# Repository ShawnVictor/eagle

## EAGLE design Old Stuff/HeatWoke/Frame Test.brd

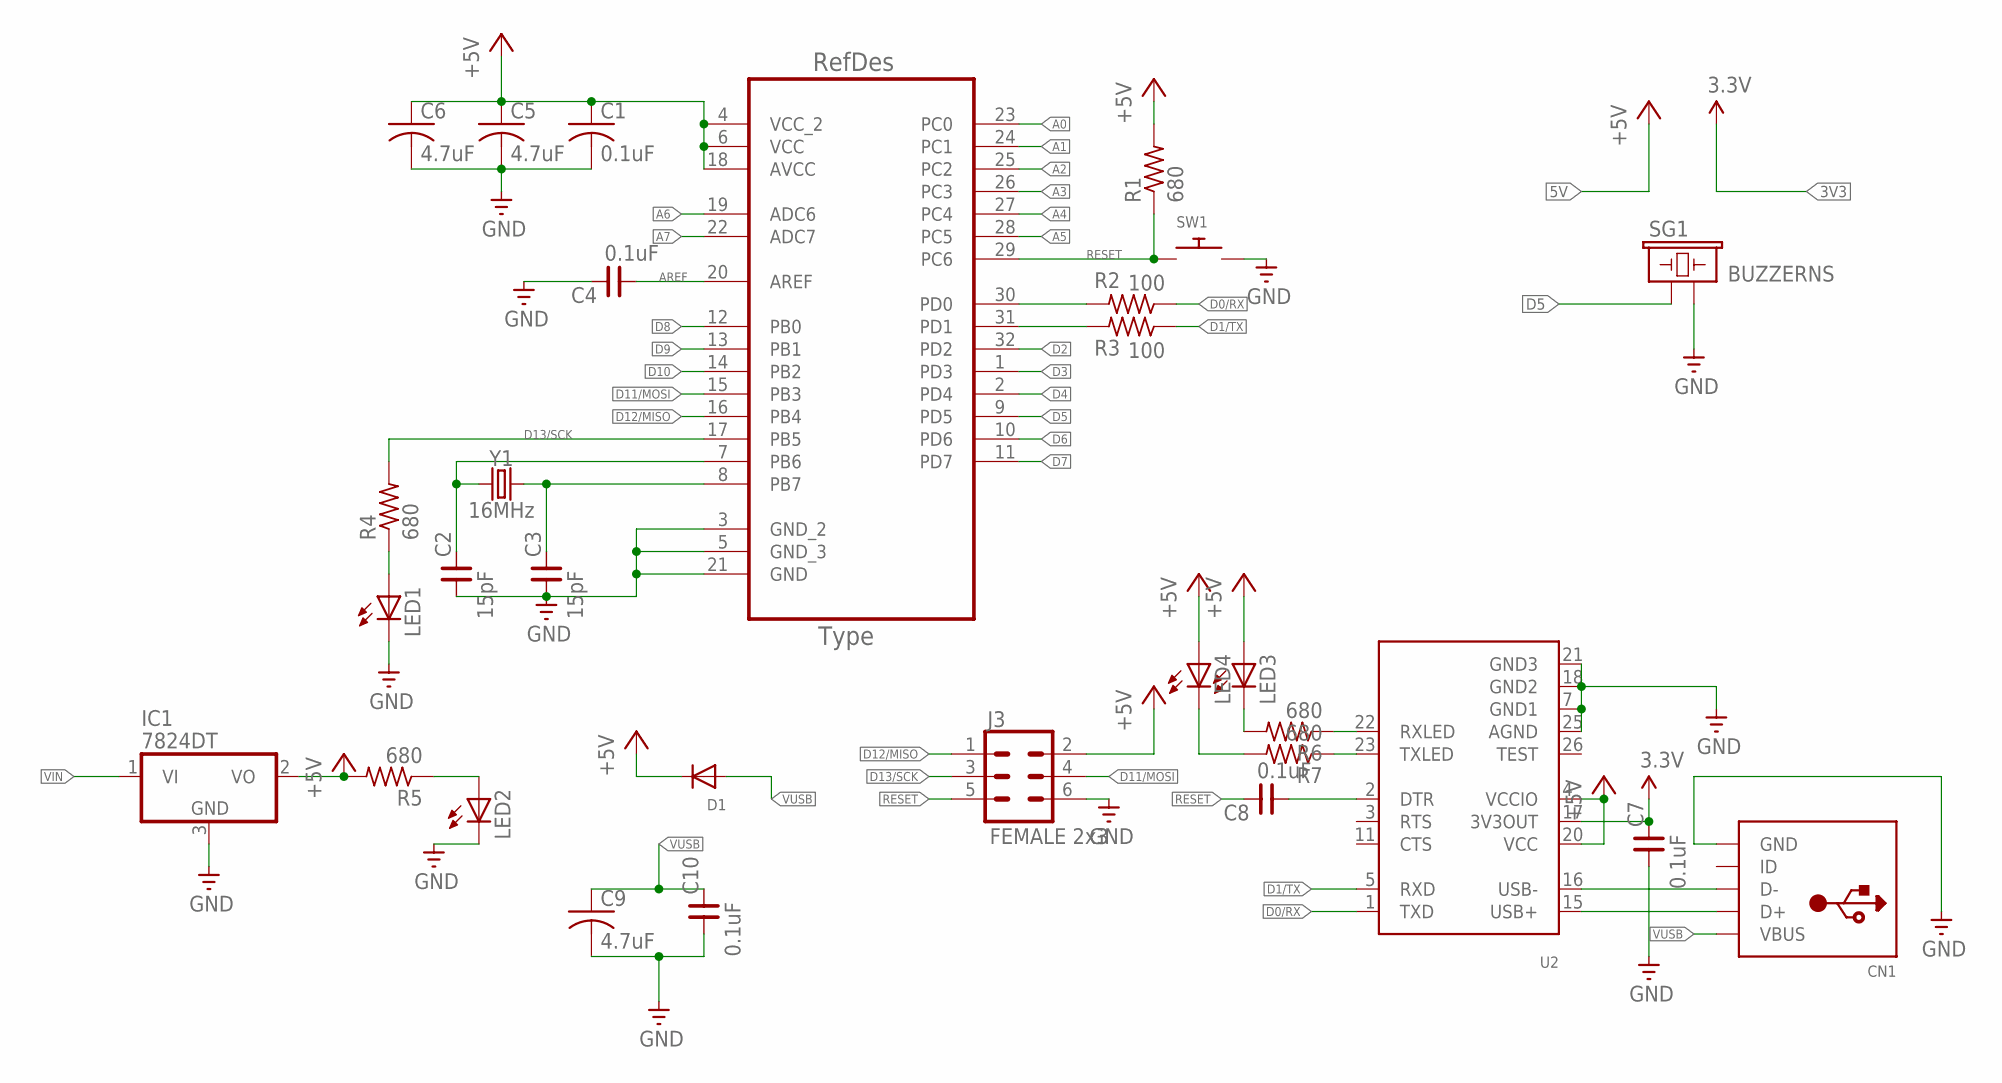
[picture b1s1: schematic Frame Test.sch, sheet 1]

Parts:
C1: 0.1uF; C0805
C2, C3: 15pF; 0805
C4, C7, C8, C10: 0.1uF; 0805
C5, C6, C9: 4.7uF; C0805
CN1: USBMINIB; USB-MINIB
D1: DIODESOD-123; SOD-123
IC1: 7824DT; TO252
J3: FEMALE 2x3; 2X3
LED1, LED2, LED3, LED4: LEDCHIPLED_0805; CHIPLED_0805
R1, R4, R5, R6, R7: 680; R0805
R2, R3: 100; R0805
SG1: BUZZERNS; BUZZER-12MM-NS
SW1: SWITCH_PUSHBUTTONEVQ-PE; TACT_PANA-EVQ
U1: ATMEGA328P-AU; QFP80P900X900X120-32N
U2: FT232RLSSOP28; SSOP28DB
Y1: 16MHz; HC49US

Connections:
3.3V: C7.2, U2.17 (3V3OUT)
+5V: C1.1, C5.1, C6.1, D1.C, IC1.2 (VO), J3.2, LED3.A, LED4.A, R1.2, R5.2, U1.4 (VCC_2), U1.6 (VCC), U1.18 (AVCC), U2.4 (VCCIO), U2.20 (VCC)
A0: U1.23 (PC0)
A1: U1.24 (PC1)
A2: U1.25 (PC2)
A3: U1.26 (PC3)
A4: U1.27 (PC4); also elsewhere on the board
A5: U1.28 (PC5); also elsewhere on the board
A6: U1.19 (ADC6)
A7: U1.22 (ADC7)
AREF: C4.1, U1.20 (AREF)
D0/RX: R2.1, U2.1 (TXD)
D1/TX: R3.1, U2.5 (RXD)
D2: U1.32 (PD2); also elsewhere on the board
D3: U1.1 (PD3); also elsewhere on the board
D4: U1.2 (PD4); also elsewhere on the board
D5: SG1.+ (1), U1.9 (PD5)
D6: U1.10 (PD6); also elsewhere on the board
D7: U1.11 (PD7)
D8: U1.12 (PB0)
D9: U1.13 (PB1)
D10: U1.14 (PB2)
D11/MOSI: J3.4, U1.15 (PB3)
D12/MISO: J3.1, U1.16 (PB4)
D13/SCK: J3.3, R4.2, U1.17 (PB5)
GND: C1.2, C2.1, C3.1, C4.2, C5.2, C6.2, C7.1, C9.2, C10.1, CN1.GND, IC1.3 (GND), J3.6, LED1.C, LED2.C, SG1.- (2), SW1.P$2, U1.3 (GND_2), U1.5 (GND_3), U1.21 (GND), U2.7 (GND1), U2.18 (GND2), U2.21 (GND3), U2.25 (AGND); also elsewhere on the board
unnamed: C3.2, U1.8 (PB7), Y1.2
unnamed: C2.2, U1.7 (PB6), Y1.1
unnamed: CN1.D+, U2.15 (USB+)
unnamed: CN1.D-, U2.16 (USB-)
unnamed: R2.2, U1.30 (PD0)
unnamed: R3.2, U1.31 (PD1)
unnamed: LED3.C, R6.2
unnamed: LED1.A, R4.1
unnamed: LED2.A, R5.1
unnamed: R6.1, U2.22 (RXLED)
unnamed: R7.1, U2.23 (TXLED)
unnamed: C8.1, U2.2 (DTR)
unnamed: LED4.C, R7.2
RESET: C8.2, J3.5, R1.1, SW1.P$1, U1.29 (PC6)
VIN: IC1.1 (VI); also elsewhere on the board
VUSB: C9.1, C10.2, CN1.VBUS, D1.A

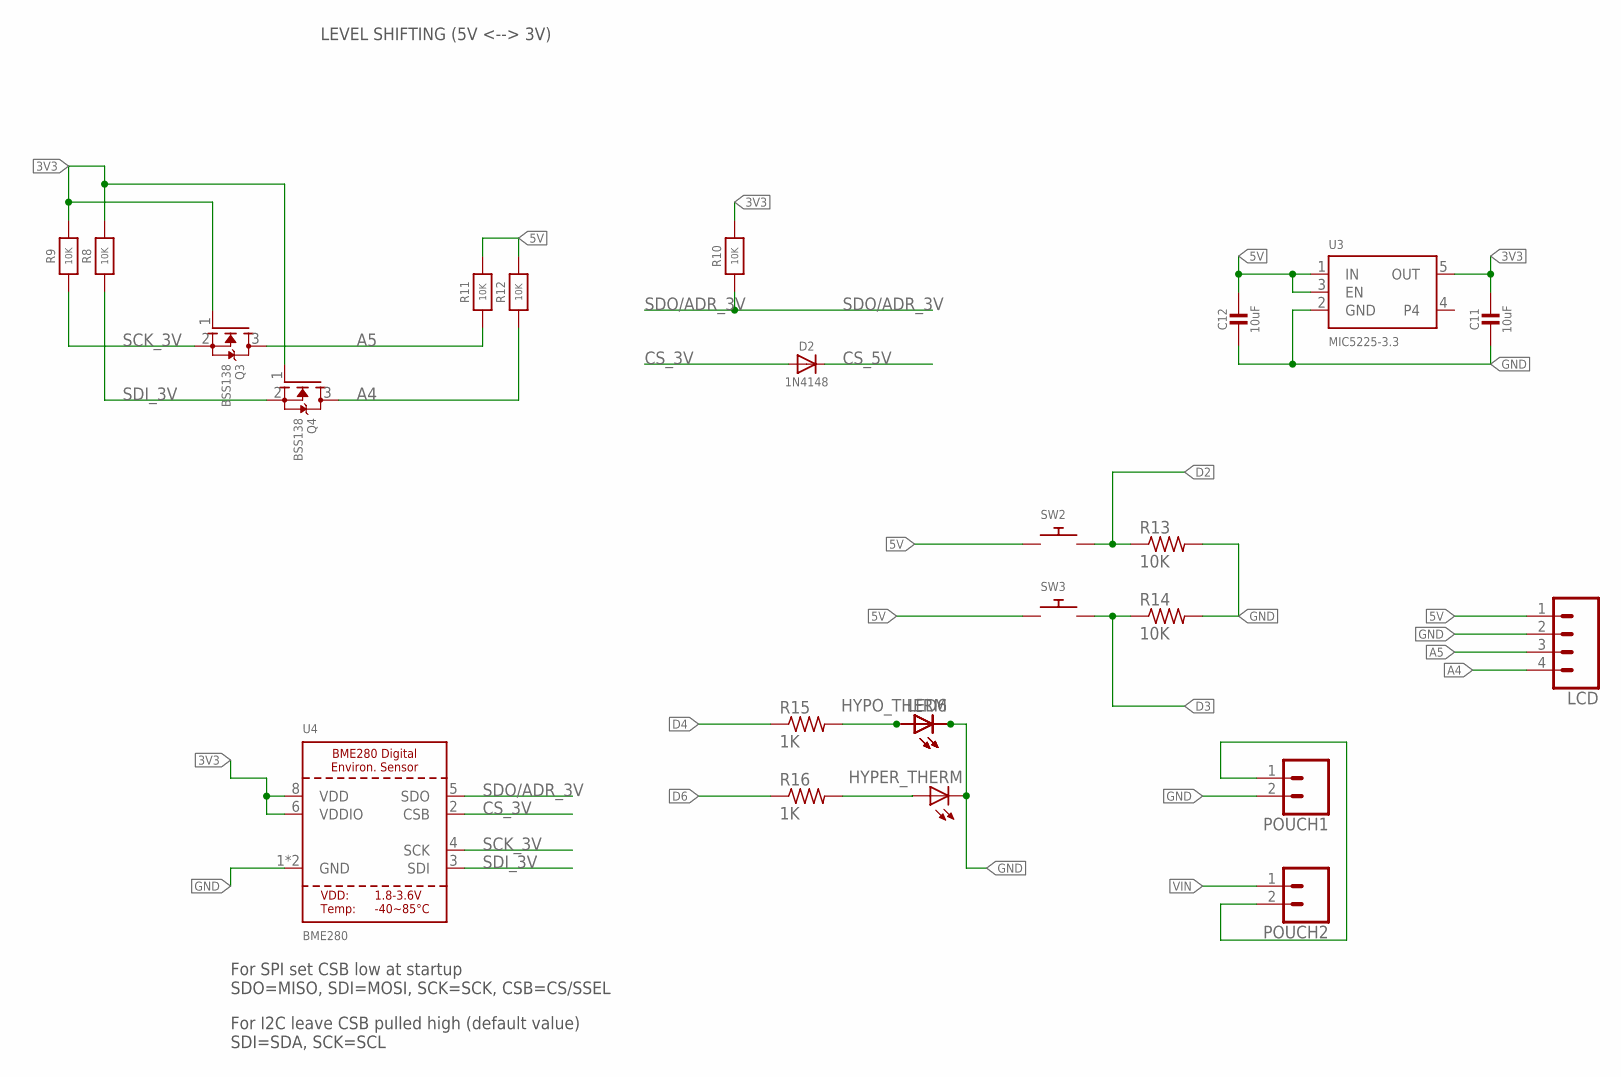
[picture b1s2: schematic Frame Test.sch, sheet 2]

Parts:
C11, C12: 10uF; 0805-NO
D2: 1N4148; SOD-323
HYPER_THERM: LEDCHIPLED_1206; CHIPLED_1206
HYPO_THERM: LEDCHIPLED_1206; CHIPLED_1206
LCD: CONN_04; 1X04
LED6: LEDCHIPLED_1206; CHIPLED_1206
POUCH1, POUCH2: CONN_02; 1X02
Q3, Q4: BSS138; SOT23-WIDE
R8, R9, R11, R12: 10K; 0805-NO
R10: 10K; _0805MP
R13, R14: 10K; R0805
R15, R16: 1K; R0805
SW2, SW3: SWITCH_PUSHBUTTONEVQ-PE; TACT_PANA-EVQ
U3: MIC5225-3.3; SOT23-5
U4: BME280

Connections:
3V3: C11.1, Q3.1 (G), Q4.1 (G), R8.2, R9.2, R10.2, U3.5 (OUT), U4.6 (VDDIO), U4.8 (VDD)
5V: C12.1, LCD.1, R11.2, R12.2, SW2.P$1, SW3.P$1, U3.1 (IN), U3.3 (EN)
A4: LCD.4, Q4.3 (D), R12.1; also elsewhere on the board
A5: LCD.3, Q3.3 (D), R11.1; also elsewhere on the board
CS_3V: D2.A, U4.2 (CSB)
CS_5V: D2.C
D2: R13.1, SW2.P$2; also elsewhere on the board
D3: R14.1, SW3.P$2; also elsewhere on the board
D4: R15.1; also elsewhere on the board
D6: R16.1; also elsewhere on the board
GND: C11.2, C12.2, HYPER_THERM.C, HYPO_THERM.C, LCD.2, LED6.C, POUCH1.2, R13.2, R14.2, U3.2 (GND), U4.1 (GND), U4.7 (GND); also elsewhere on the board
unnamed: POUCH1.1, POUCH2.2
unnamed: HYPO_THERM.A, LED6.A, R15.2
unnamed: HYPER_THERM.A, R16.2
SCK_3V: Q3.2 (S), R9.1, U4.4 (SCK)
SDI_3V: Q4.2 (S), R8.1, U4.3 (SDI)
SDO/ADR_3V: R10.1, U4.5 (SDO)
VIN: POUCH2.1; also elsewhere on the board

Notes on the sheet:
For SPI set CSB low at startup SDO=MISO, SDI=MOSI, SCK=SCK, CSB=CS/SSEL
For I2C leave CSB pulled high (default value) SDI=SDA, SCK=SCL
LEVEL SHIFTING (5V <--> 3V)

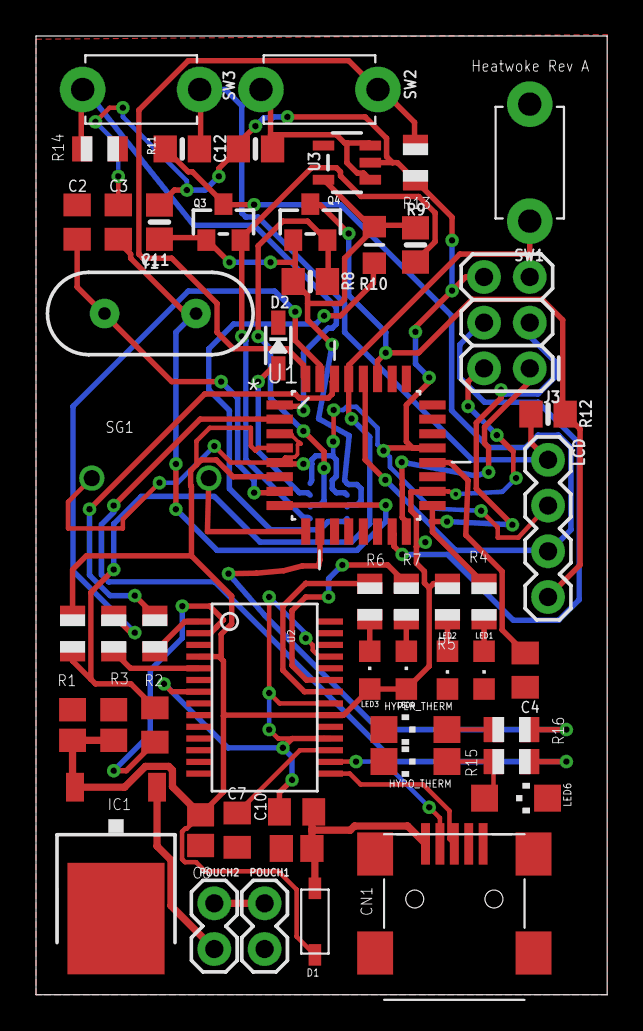
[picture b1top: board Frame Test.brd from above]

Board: 2 copper layers, 31.7 x 53.3 mm, 54 parts (1 on the bottom side), 41 nets.

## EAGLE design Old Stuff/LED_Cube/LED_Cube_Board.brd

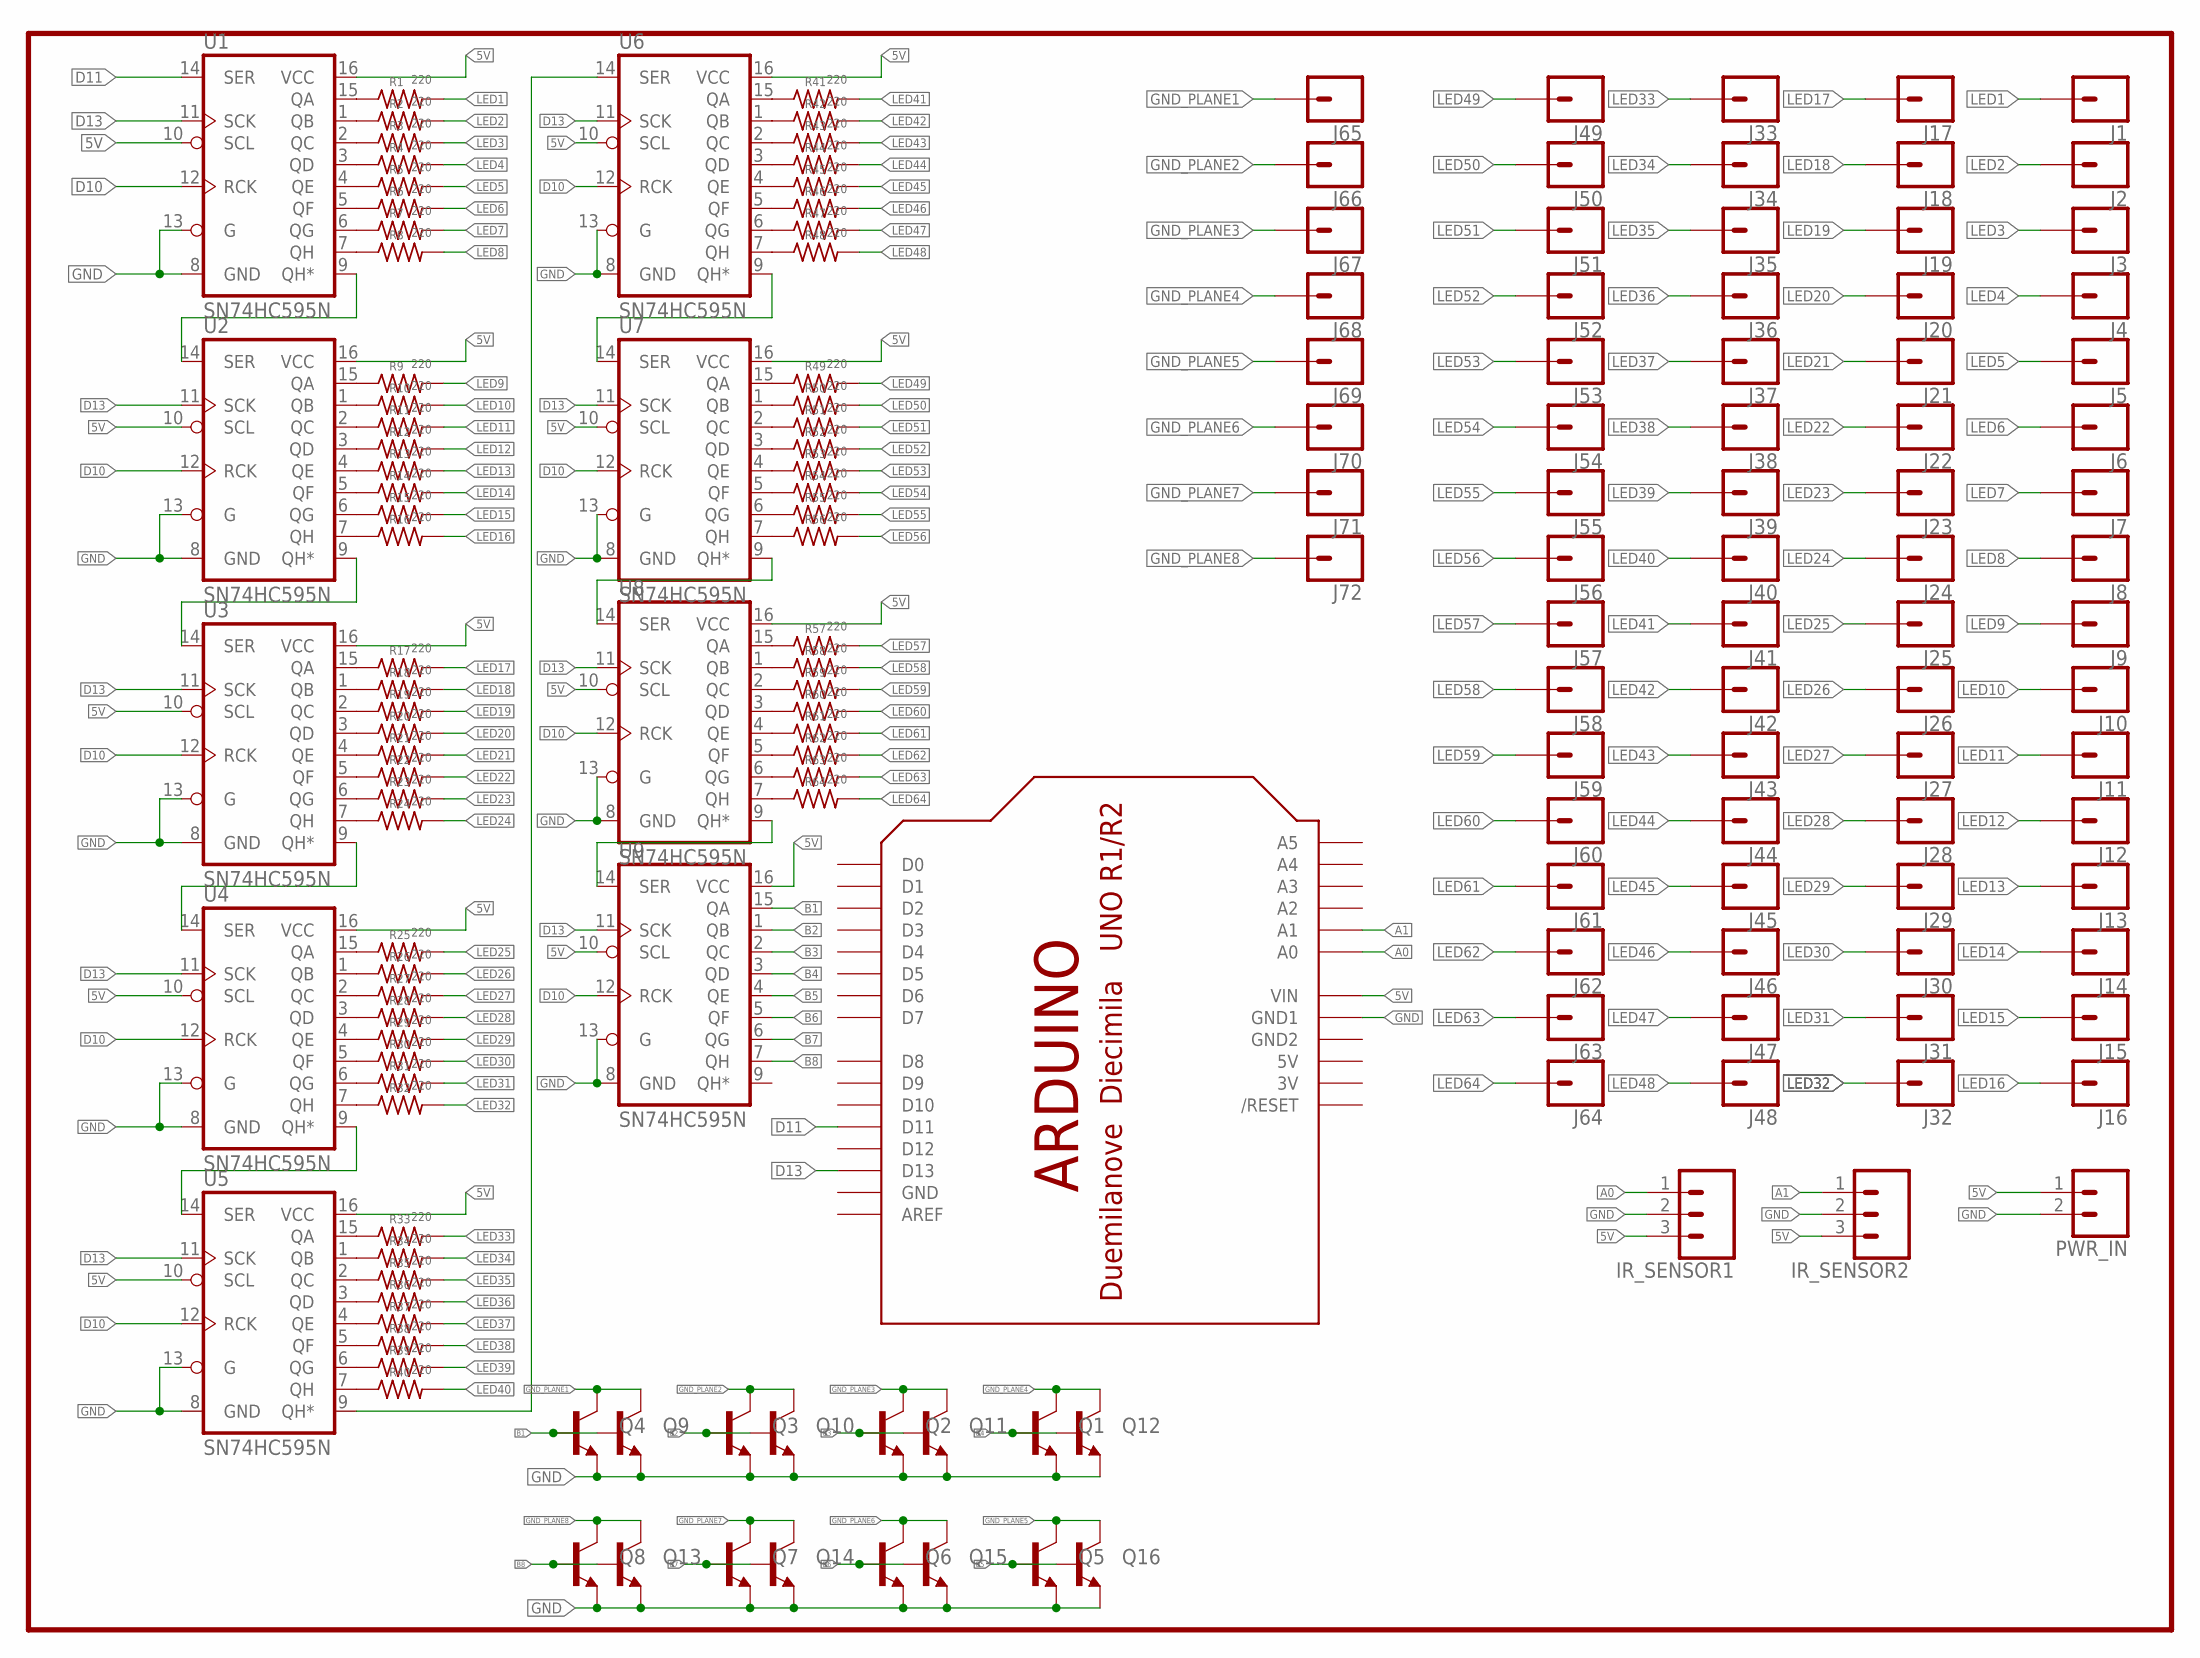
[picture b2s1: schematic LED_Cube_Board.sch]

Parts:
IR_SENSOR1, IR_SENSOR2: CONN_03; 1X03
J1, J2, J3, J4, J5, J6, J7, J8, J9, J10, J11, J12, J13, J14, J15, J16, J17, J18, J19, J20, J21, J22, J23, J24, J25, J26, J27, J28, J29, J30, J31, J32, J33, J34, J35, J36, J37, J38, J39, J40, J41, J42, J43, J44, J45, J46, J47, J48, J49, J50, J51, J52, J53, J54, J55, J56, J57, J58, J59, J60, J61, J62, J63, J64, J65, J66, J67, J68, J69, J70, J71, J72: CONN_01; 1X01
PWR_IN: CONN_02; 1X02
Q1, Q2, Q3, Q4, Q5, Q6, Q7, Q8, Q9, Q10, Q11, Q12, Q13, Q14, Q15, Q16: TRANSISTOR_NPNTO92; TO-92
R1, R2, R3, R4, R5, R6, R7, R8, R9, R10, R11, R12, R13, R14, R15, R16, R17, R18, R19, R20, R21, R22, R23, R24, R25, R26, R27, R28, R29, R30, R31, R32, R33, R34, R35, R36, R37, R38, R39, R40, R41, R42, R43, R44, R45, R46, R47, R48, R49, R50, R51, R52, R53, R54, R55, R56, R57, R58, R59, R60, R61, R62, R63, R64: 220; R0805
U1, U2, U3, U4, U5, U6, U7, U8, U9: SN74HC595N; DIP16
U$1: ARDUINO-BPLACE

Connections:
3V: U$1.3V
5V: IR_SENSOR1.3, IR_SENSOR2.3, PWR_IN.1, U1.10 (SCL), U1.16 (VCC), U2.10 (SCL), U2.16 (VCC), U3.10 (SCL), U3.16 (VCC), U4.10 (SCL), U4.16 (VCC), U5.10 (SCL), U5.16 (VCC), U6.10 (SCL), U6.16 (VCC), U7.10 (SCL), U7.16 (VCC), U8.10 (SCL), U8.16 (VCC), U9.10 (SCL), U9.16 (VCC), U$1.5V, U$1.VIN
A0: IR_SENSOR1.1, U$1.A0
A1: IR_SENSOR2.1, U$1.A1
B1: Q4.2 (B), Q9.2 (B), U9.15 (QA)
B2: Q3.2 (B), Q10.2 (B), U9.1 (QB)
B3: Q2.2 (B), Q11.2 (B), U9.2 (QC)
B4: Q1.2 (B), Q12.2 (B), U9.3 (QD)
B5: Q5.2 (B), Q16.2 (B), U9.4 (QE)
B6: Q6.2 (B), Q15.2 (B), U9.5 (QF)
B7: Q7.2 (B), Q14.2 (B), U9.6 (QG)
B8: Q8.2 (B), Q13.2 (B), U9.7 (QH)
D10: U1.12 (RCK), U2.12 (RCK), U3.12 (RCK), U4.12 (RCK), U5.12 (RCK), U6.12 (RCK), U7.12 (RCK), U8.12 (RCK), U9.12 (RCK)
D11: U1.14 (SER), U$1.D11
D13: U1.11 (SCK), U2.11 (SCK), U3.11 (SCK), U4.11 (SCK), U5.11 (SCK), U6.11 (SCK), U7.11 (SCK), U8.11 (SCK), U9.11 (SCK), U$1.D13
GND: IR_SENSOR1.2, IR_SENSOR2.2, PWR_IN.2, Q1.1 (E), Q2.1 (E), Q3.1 (E), Q4.1 (E), Q5.1 (E), Q6.1 (E), Q7.1 (E), Q8.1 (E), Q9.1 (E), Q10.1 (E), Q11.1 (E), Q12.1 (E), Q13.1 (E), Q14.1 (E), Q15.1 (E), Q16.1 (E), U1.8 (GND), U1.13 (G), U2.8 (GND), U2.13 (G), U3.8 (GND), U3.13 (G), U4.8 (GND), U4.13 (G), U5.8 (GND), U5.13 (G), U6.8 (GND), U6.13 (G), U7.8 (GND), U7.13 (G), U8.8 (GND), U8.13 (G), U9.8 (GND), U9.13 (G), U$1.GND, U$1.GND1
GND2: U$1.GND2
GND_PLANE1: J65.1, Q4.3 (C), Q9.3 (C)
GND_PLANE2: J66.1, Q3.3 (C), Q10.3 (C)
GND_PLANE3: J67.1, Q2.3 (C), Q11.3 (C)
GND_PLANE4: J68.1, Q1.3 (C), Q12.3 (C)
GND_PLANE5: J69.1, Q5.3 (C), Q16.3 (C)
GND_PLANE6: J70.1, Q6.3 (C), Q15.3 (C)
GND_PLANE7: J71.1, Q7.3 (C), Q14.3 (C)
GND_PLANE8: J72.1, Q8.3 (C), Q13.3 (C)
LED1: J1.1, R1.2
LED2: J2.1, R2.2
LED3: J3.1, R3.2
LED4: J4.1, R4.2
LED5: J5.1, R5.2
LED6: J6.1, R6.2
LED7: J7.1, R7.2
LED8: J8.1, R8.2
LED9: J9.1, R9.2
LED10: J10.1, R10.2
LED11: J11.1, R11.2
LED12: J12.1, R12.2
LED13: J13.1, R13.2
LED14: J14.1, R14.2
LED15: J15.1, R15.2
LED16: J16.1, R16.2
LED17: J17.1, R17.2
LED18: J18.1, R18.2
LED19: J19.1, R19.2
LED20: J20.1, R20.2
LED21: J21.1, R21.2
LED22: J22.1, R22.2
LED23: J23.1, R23.2
LED24: J24.1, R24.2
LED25: J25.1, R25.2
LED26: J26.1, R26.2
LED27: J27.1, R27.2
LED28: J28.1, R28.2
LED29: J29.1, R29.2
LED30: J30.1, R30.2
LED31: J31.1, R31.2
LED32: J32.1, R32.2
LED33: J33.1, R33.2
LED34: J34.1, R34.2
LED35: J35.1, R35.2
LED36: J36.1, R36.2
LED37: J37.1, R37.2
LED38: J38.1, R38.2
LED39: J39.1, R39.2
LED40: J40.1, R40.2
LED41: J41.1, R41.2
LED42: J42.1, R42.2
LED43: J43.1, R43.2
LED44: J44.1, R44.2
LED45: J45.1, R45.2
LED46: J46.1, R46.2
LED47: J47.1, R47.2
LED48: J48.1, R48.2
LED49: J49.1, R49.2
LED50: J50.1, R50.2
LED51: J51.1, R51.2
LED52: J52.1, R52.2
LED53: J53.1, R53.2
LED54: J54.1, R54.2
LED55: J55.1, R55.2
LED56: J56.1, R56.2
LED57: J57.1, R57.2
LED58: J58.1, R58.2
LED59: J59.1, R59.2
LED60: J60.1, R60.2
LED61: J61.1, R61.2
LED62: J62.1, R62.2
LED63: J63.1, R63.2
LED64: J64.1, R64.2
unnamed: R1.1, U1.15 (QA)
unnamed: R2.1, U1.1 (QB)
unnamed: R3.1, U1.2 (QC)
unnamed: U1.9 (QH*), U2.14 (SER)
unnamed: U2.9 (QH*), U3.14 (SER)
unnamed: U3.9 (QH*), U4.14 (SER)
unnamed: U4.9 (QH*), U5.14 (SER)
unnamed: U5.9 (QH*), U6.14 (SER)
unnamed: U6.9 (QH*), U7.14 (SER)
unnamed: U7.9 (QH*), U8.14 (SER)
unnamed: R4.1, U1.3 (QD)
unnamed: R5.1, U1.4 (QE)
unnamed: R6.1, U1.5 (QF)
unnamed: R7.1, U1.6 (QG)
unnamed: R8.1, U1.7 (QH)
unnamed: R9.1, U2.15 (QA)
unnamed: R10.1, U2.1 (QB)
unnamed: R11.1, U2.2 (QC)
unnamed: R12.1, U2.3 (QD)
unnamed: R13.1, U2.4 (QE)
unnamed: R14.1, U2.5 (QF)
unnamed: R15.1, U2.6 (QG)
unnamed: R16.1, U2.7 (QH)
unnamed: R17.1, U3.15 (QA)
unnamed: R18.1, U3.1 (QB)
unnamed: R19.1, U3.2 (QC)
unnamed: R20.1, U3.3 (QD)
unnamed: R21.1, U3.4 (QE)
unnamed: R22.1, U3.5 (QF)
unnamed: R23.1, U3.6 (QG)
unnamed: R24.1, U3.7 (QH)
unnamed: R25.1, U4.15 (QA)
unnamed: R26.1, U4.1 (QB)
unnamed: R27.1, U4.2 (QC)
unnamed: R28.1, U4.3 (QD)
unnamed: R29.1, U4.4 (QE)
unnamed: R30.1, U4.5 (QF)
unnamed: R31.1, U4.6 (QG)
unnamed: R32.1, U4.7 (QH)
unnamed: R33.1, U5.15 (QA)
unnamed: R34.1, U5.1 (QB)
unnamed: R35.1, U5.2 (QC)
unnamed: R36.1, U5.3 (QD)
unnamed: R37.1, U5.4 (QE)
unnamed: R38.1, U5.5 (QF)
unnamed: R39.1, U5.6 (QG)
unnamed: R40.1, U5.7 (QH)
unnamed: R41.1, U6.15 (QA)
unnamed: R42.1, U6.1 (QB)
unnamed: R43.1, U6.2 (QC)
unnamed: R44.1, U6.3 (QD)
unnamed: R45.1, U6.4 (QE)
unnamed: R46.1, U6.5 (QF)
unnamed: R47.1, U6.6 (QG)
unnamed: R48.1, U6.7 (QH)
unnamed: R49.1, U7.15 (QA)
unnamed: R50.1, U7.1 (QB)
unnamed: R51.1, U7.2 (QC)
unnamed: R52.1, U7.3 (QD)
unnamed: R53.1, U7.4 (QE)
unnamed: R54.1, U7.5 (QF)
unnamed: R55.1, U7.6 (QG)
unnamed: R56.1, U7.7 (QH)
unnamed: R57.1, U8.15 (QA)
unnamed: R58.1, U8.1 (QB)
unnamed: R59.1, U8.2 (QC)
unnamed: R60.1, U8.3 (QD)
unnamed: R61.1, U8.4 (QE)
unnamed: R62.1, U8.5 (QF)
unnamed: R63.1, U8.6 (QG)
unnamed: R64.1, U8.7 (QH)
unnamed: U8.9 (QH*), U9.14 (SER)

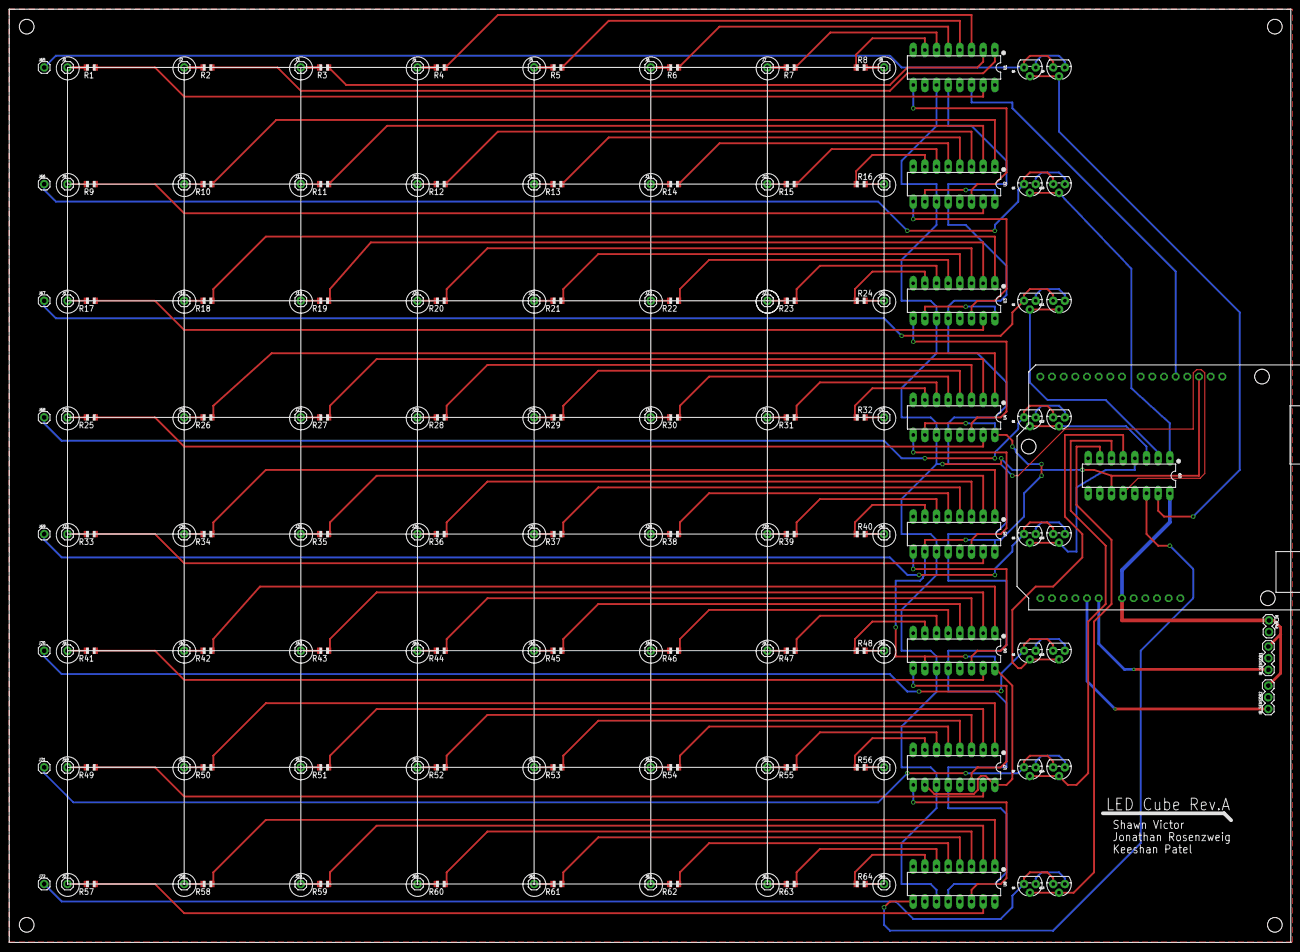
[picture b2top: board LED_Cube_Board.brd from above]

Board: 2 copper layers, 279.1 x 203.2 mm, 165 parts (1 on the bottom side), 159 nets.

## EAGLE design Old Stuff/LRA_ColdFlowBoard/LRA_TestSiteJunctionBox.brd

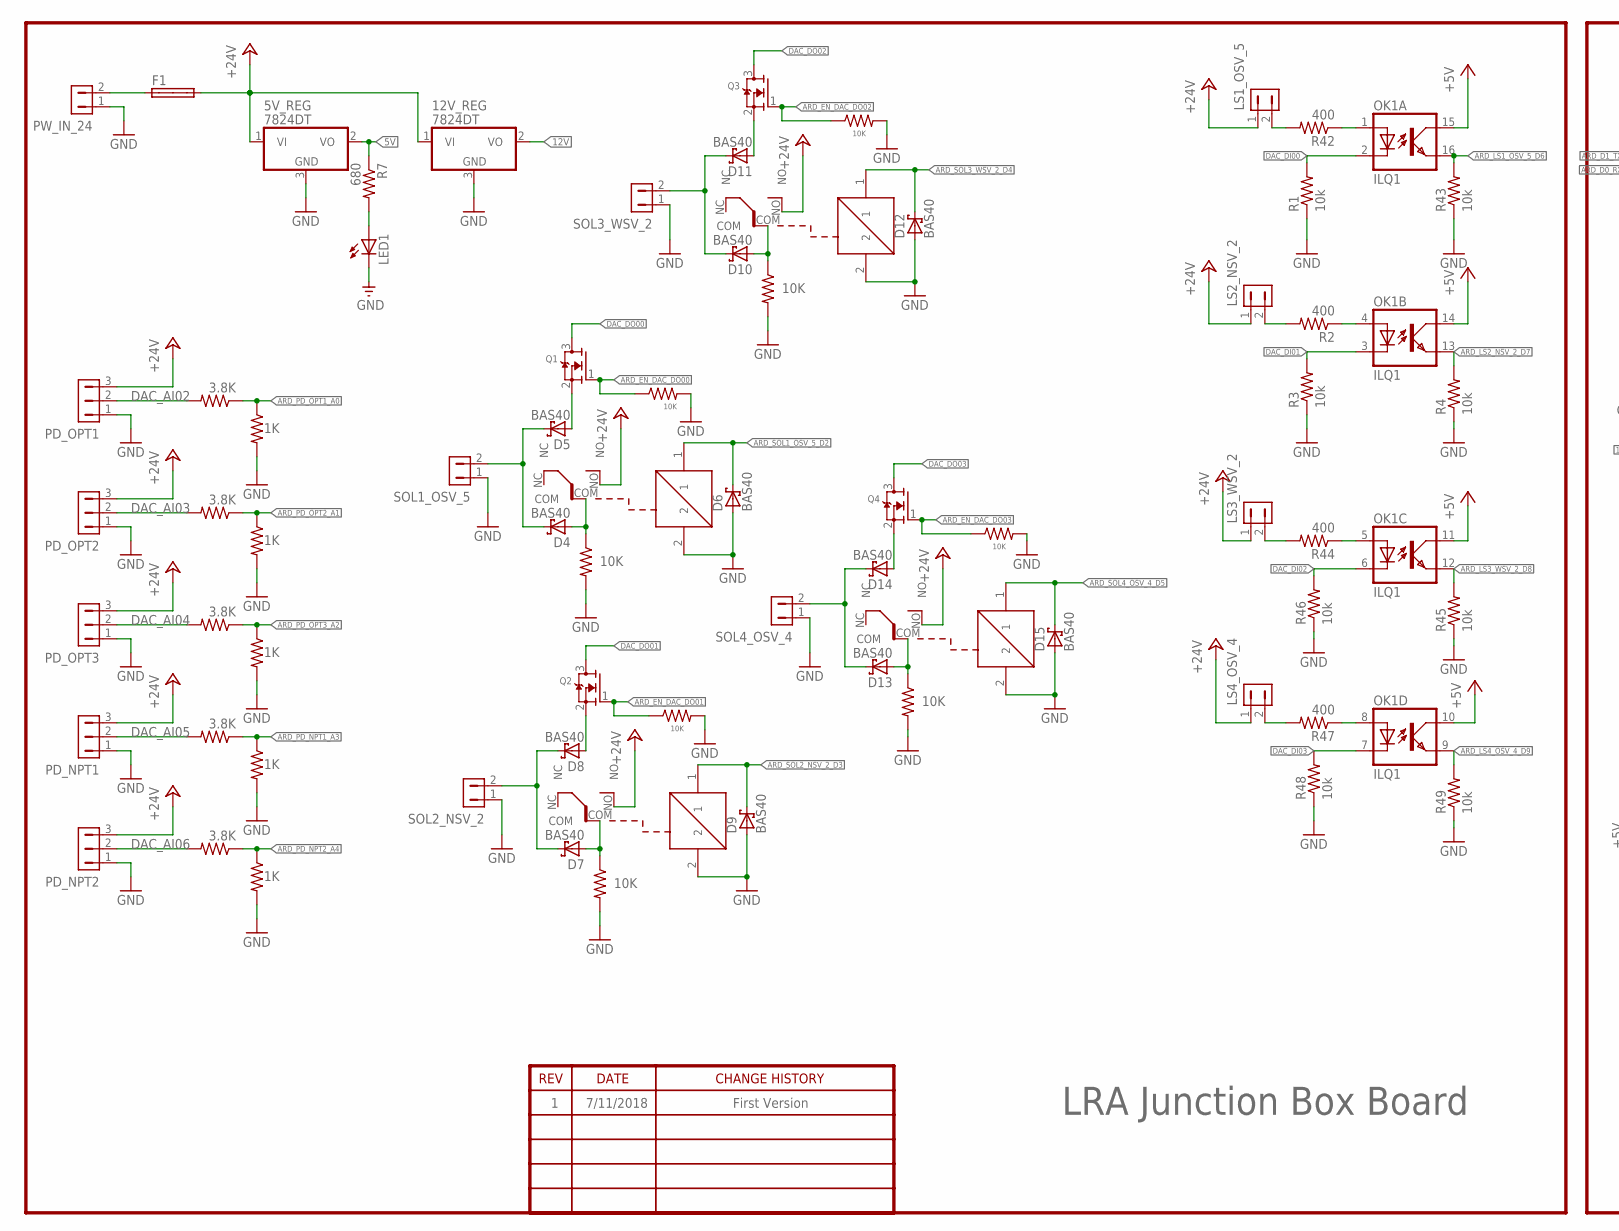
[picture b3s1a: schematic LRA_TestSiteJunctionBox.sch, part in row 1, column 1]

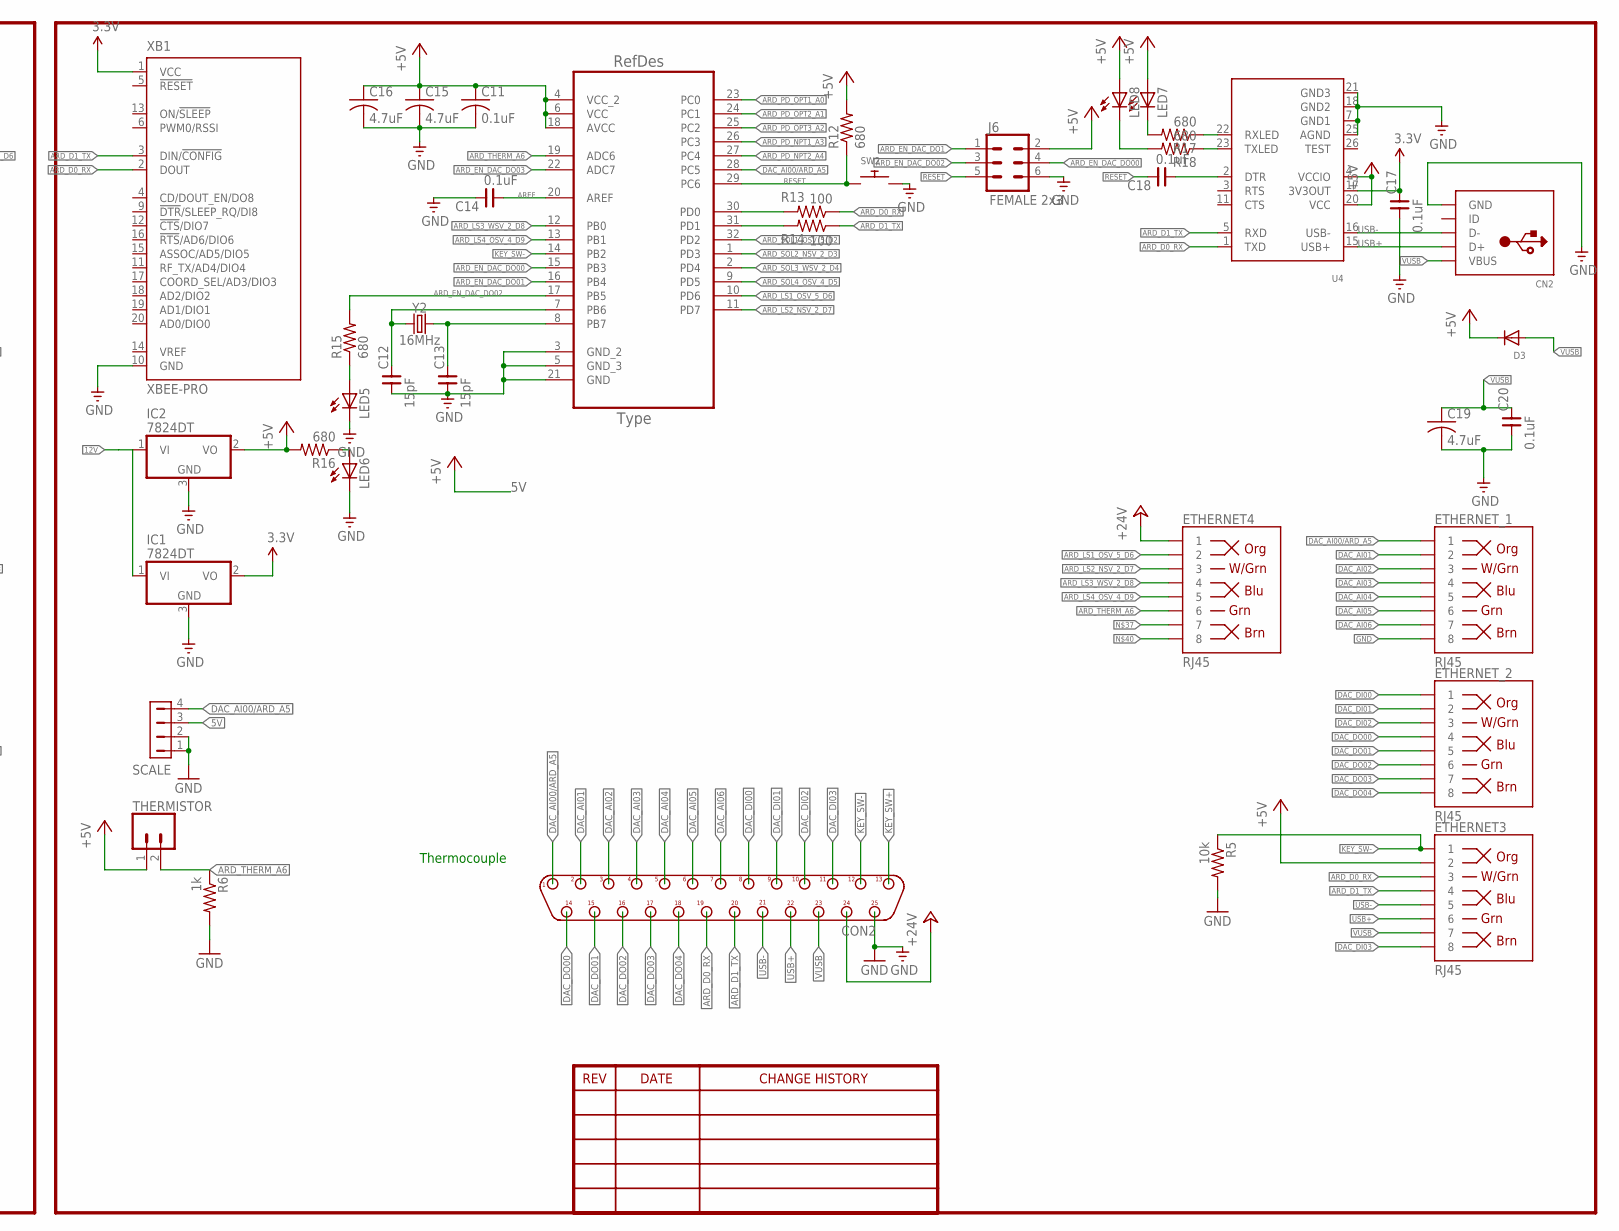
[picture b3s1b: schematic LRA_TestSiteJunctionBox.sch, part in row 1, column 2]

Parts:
5V_REG, 12V_REG: 7824DT; TO252
C11: 0.1uF; C0805
C12, C13: 15pF; 0805
C14, C17, C18, C20: 0.1uF; 0805
C15, C16, C19: 4.7uF; C0805
CN2: USBMINIB; USB-MINIB
CON2: DB25M/90; D-25M/90
D3: DIODESOD-123; SOD-123
D4, D5, D6, D7, D8, D9, D10, D11, D12, D13, D14, D15: BAS40; SOT23
ETHERNET3, ETHERNET4: RJ45; RJ45-8
ETHERNET_1, ETHERNET_2: RJ45; RJ45-8
F1: SHK20L
IC1, IC2: 7824DT; TO252
J6: FEMALE 2x3; 2X3
LED1, LED5, LED6, LED7, LED8: LEDCHIPLED_0805; CHIPLED_0805
LS1_OSV_5, LS2_NSV_2, LS3_WSV_2, LS4_OSV_4: HDR-1X2-MTA-100; MTA-100-2V
OK1: ILQ1; DIL16
PD_NPT1, PD_NPT2: HDR-1X3-MTA-100; MTA-100-3V
PD_OPT1, PD_OPT2, PD_OPT3: HDR-1X3-MTA-100; MTA-100-3V
PW_IN_24: HDR-1X2-MTA-100; MTA-100-2V
Q1, Q2, Q3, Q4: MOSFET-NREFLOW; SOT23
R1, R3, R4, R43, R45, R46, R48, R49: 10k; M0805
R2, R42, R44, R47: 400; M0805
R5: 10k; R0805
R6: 1k; R0805
R7, R12, R15, R16, R17, R18: 680; R0805
R13, R14: 100; R0805
R24, R26, R28, R30, R32: 3.8K; M0805
R25, R27, R29, R31, R33: 1K; M0805
R34, R35, R36, R37, R38, R39, R40, R41: 10K; M0805
SCALE: HDR-1X4-MTA-100; MTA-100-4V
SOL1_OSV_5, SOL2_NSV_2, SOL3_WSV_2, SOL4_OSV_4: HDR-1X2-MTA-100; MTA-100-2V
SW2: SWITCH_PUSHBUTTONEVQ-PE; TACT_PANA-EVQ
THERMISTOR: CONN_025MM; SCREWTERMINAL-5MM-2
U3: ATMEGA328P-AU; QFP80P900X900X120-32N
U4: FT232RLSSOP28; SSOP28DB
U$2, U$3, U$4, U$5: RW-SH
XB1: XBEE-PRO
Y2: 16MHz; HC49US

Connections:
3.3V: C17.2, IC1.2 (VO), U4.17 (3V3OUT), XB1.1 (VCC)
5V: 5V_REG.2 (VO), R7.1, SCALE.3
12V: 12V_REG.2 (VO), IC1.1 (VI), IC2.1 (VI)
+5V: C11.1, C15.1, C16.1, D3.C, ETHERNET3.2, IC2.2 (VO), J6.2, LED7.A, LED8.A, OK1.10 (COL), OK1.11 (COL), OK1.14 (COL), OK1.15 (COL), R12.2, R16.2, THERMISTOR.1, U3.4 (VCC_2), U3.6 (VCC), U3.18 (AVCC), U4.4 (VCCIO), U4.20 (VCC)
+24V: 5V_REG.1 (VI), 12V_REG.1 (VI), CON2.24, ETHERNET4.1, F1.2A, LS1_OSV_5.1, LS2_NSV_2.1, LS3_WSV_2.1, LS4_OSV_4.1, PD_NPT1.3, PD_NPT2.3, PD_OPT1.3, PD_OPT2.3, PD_OPT3.3, U$2.NO, U$3.NO, U$4.NO, U$5.NO
ARD_D0_RX: CON2.19, ETHERNET3.3, R13.1, U4.1 (TXD), XB1.2 (DOUT)
ARD_D1_TX: CON2.20, ETHERNET3.4, R14.1, U4.5 (RXD), XB1.3 (DIN/!CONFIG)
ARD_EN_DAC_DO00: J6.4, Q1.1 (G), R39.1, U3.15 (PB3)
ARD_EN_DAC_DO1: J6.1
ARD_EN_DAC_DO01: Q2.1 (G), R38.1, U3.16 (PB4)
ARD_EN_DAC_DO02: J6.3, Q3.1 (G), R15.2, R40.1, U3.17 (PB5)
ARD_EN_DAC_DO03: Q4.1 (G), R41.1, U3.22 (ADC7)
ARD_LS1_OSV_5_D6: ETHERNET4.2, OK1.16 (EMIT), R43.2, U3.10 (PD6)
ARD_LS2_NSV_2_D7: ETHERNET4.3, OK1.13 (EMIT), R4.2, U3.11 (PD7)
ARD_LS3_WSV_2_D8: ETHERNET4.4, OK1.12 (EMIT), R45.2, U3.12 (PB0)
ARD_LS4_OSV_4_D9: ETHERNET4.5, OK1.9 (EMIT), R49.2, U3.13 (PB1)
ARD_PD_NPT1_A3: R30.1, R31.1, U3.26 (PC3)
ARD_PD_NPT2_A4: R32.1, R33.1, U3.27 (PC4)
ARD_PD_OPT1_A0: R24.1, R25.1, U3.23 (PC0)
ARD_PD_OPT2_A1: R26.1, R27.1, U3.24 (PC1)
ARD_PD_OPT3_A2: R28.1, R29.1, U3.25 (PC2)
ARD_SOL1_OSV_5_D2: D6.3 (C), U3.32 (PD2), U$2.1
ARD_SOL2_NSV_2_D3: D9.3 (C), U3.1 (PD3), U$3.1
ARD_SOL3_WSV_2_D4: D12.3 (C), U3.2 (PD4), U$4.1
ARD_SOL4_OSV_4_D5: D15.3 (C), U3.9 (PD5), U$5.1
ARD_THERM_A6: ETHERNET4.6, R6.1, THERMISTOR.2, U3.19 (ADC6)
AREF: C14.1, U3.20 (AREF)
DAC_AI00/ARD_A5: CON2.1, ETHERNET_1.1, SCALE.4, U3.28 (PC5)
DAC_AI01: CON2.2, ETHERNET_1.2
DAC_AI02: CON2.3, ETHERNET_1.3, PD_OPT1.2, R24.2
DAC_AI03: CON2.4, ETHERNET_1.4, PD_OPT2.2, R26.2
DAC_AI04: CON2.5, ETHERNET_1.5, PD_OPT3.2, R28.2
DAC_AI05: CON2.6, ETHERNET_1.6, PD_NPT1.2, R30.2
DAC_AI06: CON2.7, ETHERNET_1.7, PD_NPT2.2, R32.2
DAC_DI00: CON2.8, ETHERNET_2.1, OK1.2 (C), R1.2
DAC_DI01: CON2.9, ETHERNET_2.2, OK1.3 (C), R3.2
DAC_DI02: CON2.10, ETHERNET_2.3, OK1.6 (C), R46.2
DAC_DI03: CON2.11, ETHERNET3.8, OK1.7 (C), R48.2
DAC_DO00: CON2.14, ETHERNET_2.4, Q1.3 (D)
DAC_DO01: CON2.15, ETHERNET_2.5, Q2.3 (D)
DAC_DO02: CON2.16, ETHERNET_2.6, Q3.3 (D)
DAC_DO03: CON2.17, ETHERNET_2.7, Q4.3 (D)
DAC_DO04: CON2.18, ETHERNET_2.8
GND: 5V_REG.3 (GND), 12V_REG.3 (GND), C11.2, C12.1, C13.1, C14.2, C15.2, C16.2, C17.1, C19.2, C20.1, CN2.GND, CON2.25, D6.1 (A), D9.1 (A), D12.1 (A), D15.1 (A), ETHERNET_1.8, IC1.3 (GND), IC2.3 (GND), J6.6, LED1.C, LED5.C, LED6.C, PD_NPT1.1, PD_NPT2.1, PD_OPT1.1, PD_OPT2.1, PD_OPT3.1, PW_IN_24.1, R1.1, R3.1, R4.1, R5.2, R6.2, R25.2, R27.2, R29.2, R31.2, R33.2, R34.2, R35.2, R36.2, R37.2, R38.2, R39.2, R40.2, R41.2, R43.1, R45.1, R46.1, R48.1, R49.1, SCALE.1, SCALE.2, SOL1_OSV_5.1, SOL2_NSV_2.1, SOL3_WSV_2.1, SOL4_OSV_4.1, SW2.P$2, U3.3 (GND_2), U3.5 (GND_3), U3.21 (GND), U4.7 (GND1), U4.18 (GND2), U4.21 (GND3), U4.25 (AGND), U$2.2, U$3.2, U$4.2, U$5.2, XB1.10 (GND)
KEY_SW+: CON2.13
KEY_SW-: CON2.12, ETHERNET3.1, R5.1, U3.14 (PB2)
unnamed: F1.1A, PW_IN_24.2
unnamed: LED1.A, R7.2
unnamed: OK1.1 (A), R42.1
unnamed: LED6.A, R16.1
unnamed: LED5.A, R15.1
unnamed: D4.3 (C), D5.3 (C), SOL1_OSV_5.2
unnamed: D7.3 (C), D8.3 (C), SOL2_NSV_2.2
unnamed: D4.1 (A), R34.1, U$2.COM
unnamed: D5.1 (A), Q1.2 (S)
unnamed: D7.1 (A), R35.1, U$3.COM
unnamed: D8.1 (A), Q2.2 (S)
unnamed: D10.3 (C), D11.3 (C), SOL3_WSV_2.2
unnamed: D10.1 (A), R36.1, U$4.COM
unnamed: D11.1 (A), Q3.2 (S)
unnamed: D13.3 (C), D14.3 (C), SOL4_OSV_4.2
unnamed: D13.1 (A), R37.1, U$5.COM
unnamed: C13.2, U3.8 (PB7), Y2.2
unnamed: C12.2, U3.7 (PB6), Y2.1
unnamed: R13.2, U3.30 (PD0)
unnamed: R14.2, U3.31 (PD1)
unnamed: R17.1, U4.22 (RXLED)
unnamed: R18.1, U4.23 (TXLED)
unnamed: LED8.C, R18.2
unnamed: LED7.C, R17.2
unnamed: C18.1, U4.2 (DTR)
unnamed: D14.1 (A), Q4.2 (S)
unnamed: LS1_OSV_5.2, R42.2
unnamed: OK1.4 (A), R2.1
unnamed: LS2_NSV_2.2, R2.2
unnamed: OK1.5 (A), R44.1
unnamed: LS3_WSV_2.2, R44.2
unnamed: OK1.8 (A), R47.1
unnamed: LS4_OSV_4.2, R47.2
RESET: C18.2, J6.5, R12.1, SW2.P$1, U3.29 (PC6)
USB+: CN2.D+, CON2.22, ETHERNET3.6, U4.15 (USB+)
USB-: CN2.D-, CON2.21, ETHERNET3.5, U4.16 (USB-)
VUSB: C19.1, C20.2, CN2.VBUS, CON2.23, D3.A, ETHERNET3.7

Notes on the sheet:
LRA Junction Box Board
7/11/2018
First Version
Thermocouple

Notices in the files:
parts and their libraries:
SparkFun-Connectors: Licensing: Creative Commons ShareAlike 4.0 International - https://creativecommons.org/licenses/by-sa/4.0
dframes: Copyright (C) 2004, Bob Starr (bobstarr@mindspring.com)
rc-master-smd: Copyright (C) 2007, Bob Starr
op-amp: Copyright (C) 2006 by Bob Starr
